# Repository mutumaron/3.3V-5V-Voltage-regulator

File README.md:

# 3.3V-5V-Voltage-regulator
12V & 5V/3.3V Dual Power Supply Module

A custom printed circuit board designed in KiCad to regulate high-voltage inputs down to clean 5V and 3.3V rails.

📝 Project Overview

This project provides a stable power foundation for microcontrollers (like the ESP32) while allowing them to control 12V peripherals. It features proper ground plane isolation, thermal reliefs, and optimized current return paths to minimize switching noise.

🖼️ Board Views

3D Render

Schematic

PCB Layout (Top & Bottom)

F.Fabrication layer

🗂️ Files Included

*.kicad_pro, *.kicad_sch, *.kicad_pcb: The raw KiCad 10 project files.

/PDFs: Downloadable PDF versions of the schematic and copper layers.

/Gerbers: (Optional) Production files ready to be sent to a manufacturer like JLCPCB.

⚙️ Key Specifications

Input Voltage: 12V DC (Barrel Jack)

Output Voltages: 12V, 5V, 3.3V

Layers: 2-Layer (F.Cu, B.Cu with solid GND plane)

Design Software: KiCad 10

🛠️ How to Use

Clone this repository.

Open the .kicad_pro file in KiCad 10 or newer.

To manufacture, zip the /Gerbers folder and upload it to your preferred fab house.

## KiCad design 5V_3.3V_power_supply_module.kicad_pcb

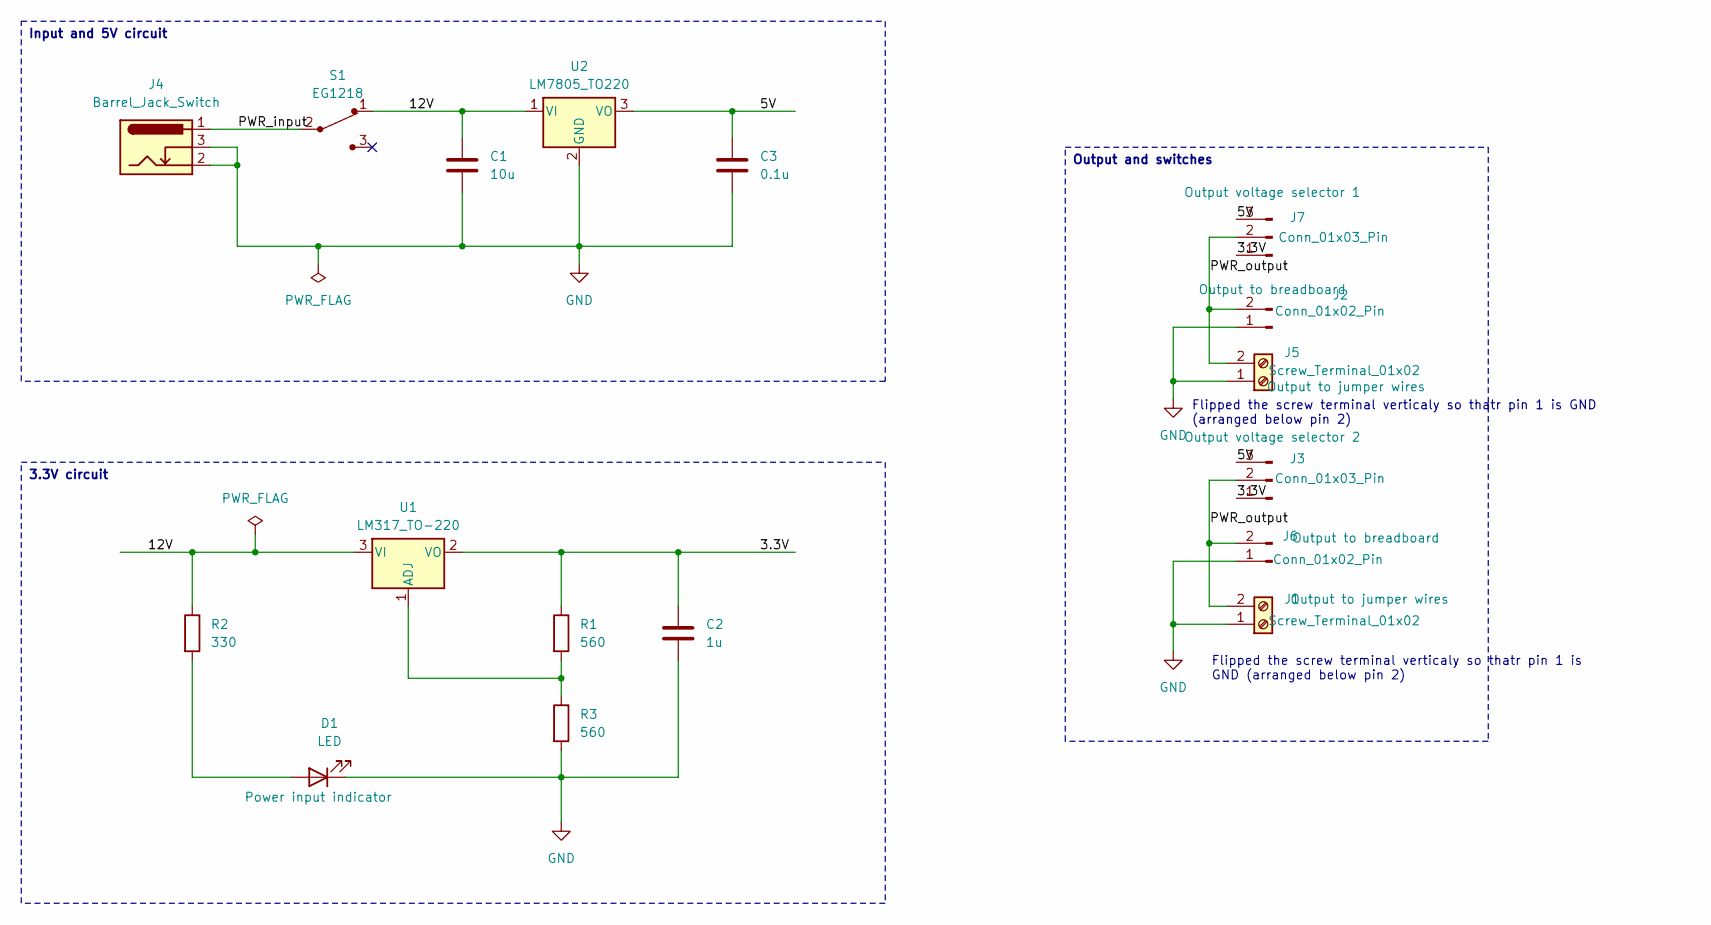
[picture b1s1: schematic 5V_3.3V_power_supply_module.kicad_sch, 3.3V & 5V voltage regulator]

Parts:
C1: 10u; C_Disc_D3.0mm_W1.6mm_P2.50mm
C2: 1u; C_Disc_D3.0mm_W1.6mm_P2.50mm
C3: 0.1u; C_Disc_D3.0mm_W1.6mm_P2.50mm
D1: LED; LED_D5.0mm
J1, J5: Screw_Terminal_01x02; Altech_AK100_1x02_P5.00mm
J2, J6: Conn_01x02_Pin; PinHeader_1x02_P2.54mm_Vertical
J3, J7: Conn_01x03_Pin; PinHeader_1x03_P2.54mm_Vertical
J4: Barrel_Jack_Switch; BarrelJack_Horizontal
R1, R3: 560; R_Axial_DIN0204_L3.6mm_D1.6mm_P7.62mm_Horizontal
R2: 330; R_Axial_DIN0204_L3.6mm_D1.6mm_P7.62mm_Horizontal
S1: EG1218; Switch_Slide_11.6x4mm_EG1218; MPN EG1218; Digi-Key_PN EG1903-ND
U1: LM317_TO-220; TO-220-3_Vertical
U2: LM7805_TO220; TO-220-3_Vertical

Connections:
/3.3V: C2.1, J3.1, J7.1, R1.1, U1.2 (VO)
/5V: C3.1, J3.3, J7.3, U2.3 (VO)
/12V: C1.1, R2.1, S1.1, U1.3 (VI), U2.1 (VI)
/PWR_input: J4.1, S1.2
/PWR_output: J1.2, J2.2, J3.2, J5.2, J6.2, J7.2
GND: C1.2, C2.2, C3.2, D1.1 (K), J1.1, J2.1, J4.2, J4.3, J5.1, J6.1, R3.2, U2.2 (GND)
unnamed: D1.2 (A), R2.2
unnamed: R1.2, R3.1, U1.1 (ADJ)

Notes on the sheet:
Flipped the screw terminal verticaly so thatr pin 1 is GND (arranged below pin 2)
Flipped the screw terminal verticaly so thatr pin 1 is GND (arranged below pin 2)
3.3V circuit
Input and 5V circuit
Output and switches

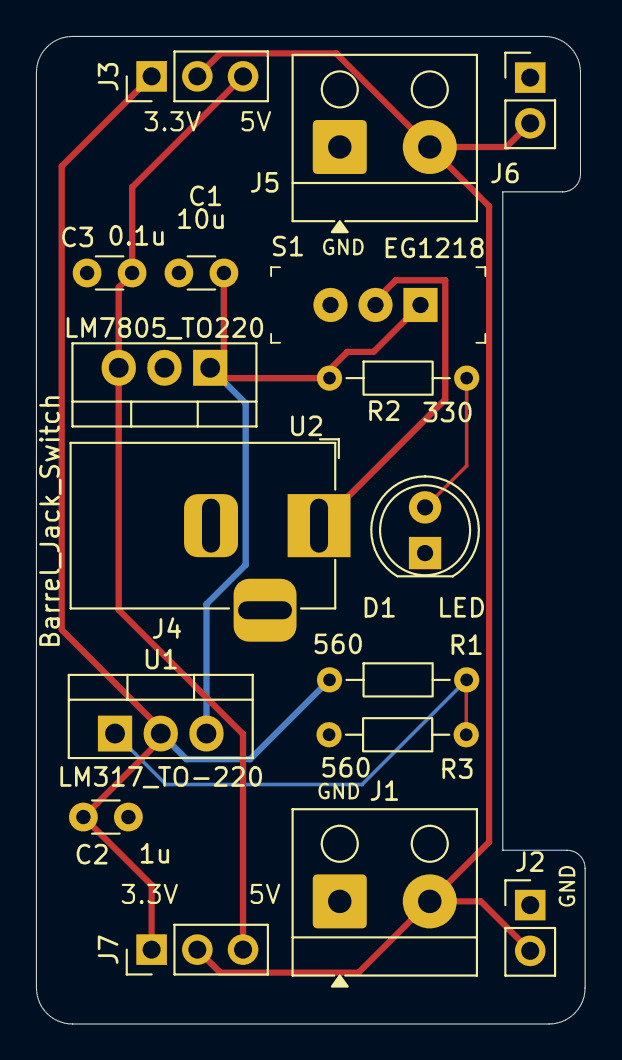
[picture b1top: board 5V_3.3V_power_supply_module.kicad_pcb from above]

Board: 2 copper layers, 30.5 x 54.9 mm, 17 parts (0 on the bottom side), 8 nets.
